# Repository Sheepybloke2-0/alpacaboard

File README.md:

# Alpaca-board
An Open Source keyboard designed for Kailh Low Profile Switches.

This keyboard is meant to be ultra portable, using the [Kailh Low Profile](https://novelkeys.xyz/products/kailh-low-profile-switches)
switches and a minimalist design. That being said, I wanted to add all the keys that I miss when typing on my 40% and 60% boards, such as arrow
keys, Home, End, Delete, Up and Down. I also decided to use USB C as the connector, since I perfer the form factor and flexablility for future
designs. The keyboard will be fully customizable through QMK, the software of which will be coming up soon.

# Goals
 - Be portable yet useful
 - Have RGB underglow, maybe backlighting?
 - Try out different PCB and key layouts for something new and exciting
 - Utilize current Kailh Low Profile switches and keycaps 
 - Add Bluetooth capablilities!

# Software and Tools
Schematic and PCB design was done in [KiCAD](http://kicad-pcb.org/). Because I'm lazy, the routing was done by [Freerouting](https://github.com/freerouting/freerouting).

# References
 - [ATmega32U4 Datasheet](https://cdn.sparkfun.com/datasheets/Dev/Arduino/Boards/ATMega32U4.pdf)
 - [PJRC Wiki](https://www.pjrc.com/)
 - [OLKB Basic Schematics](https://github.com/olkb/olkb_parts/blob/master/planck/schematic.pdf)
    - Used this as a basic reference on how to use the ATmega in the system. Great starting point for figuring out what to Google!
 - [Kailh Low Profile CAD](https://github.com/keyboardio/keyswitch_documentation/blob/master/datasheets/Kailh/PG135001D02.pdf)
    - I believe this is still the design of the current switches. 
 - [QMK's handwiring guide](https://docs.qmk.fm/#/hand_wire)
    - Helps you understand the basics of keyboard design and the key matrix
 - [USB C connector pinouts](https://en.wikipedia.org/wiki/USB-C#Connector_pinouts)
 - [Guide to the key matrix](http://blog.komar.be/how-to-make-a-keyboard-the-matrix/)
    - Great and informative guide to keyboard design
 - [Featherwing ATmega32u4 with BLE](https://www.adafruit.com/product/2829)
 - [MCP23008 I2C GPIO Expander](https://www.adafruit.com/product/593)
 - [Max keyboard key size chart](http://www.maxkeyboard.com/mechanical-keycap-layout-and-size-chart.html)
 - [Bunch of keyboard parts](https://github.com/keebio/Keebio-Parts.pretty)
 - [Featherwing KiCAD Model](https://forum.kicad.info/t/designing-featherwings-in-kicad/6115/2)
    - Use the bottom one
    
# Version 0.2 
After making the schematic and layout for V0.1, I decided to change the components to thru-hole and use a micro-controller for 
easier soldering and assembly. The other reason is because of the Featherwing ATMega32u4 with BLE support. This has a handle
LiPo charging circuit and BLE support for most devices, specifically mobile. For some computers a converter may be needed. 
However, in order to make this work, I had to add a GPIO expander, since most of the pins on the Featherwing are needed for
other functions, such as the Bluetooth and charging. The expander talks via I2C and is addressed at `000`. This expander also
allows for the RGB underglow I wanted to include. Now, it's on to fabrication and software!

# License
I hope that by keeping this project Open Source, other designers can use my work as a base to get up and running quickly. Feel free to use my 
notes and ideas, but please adhere to the [Open Hardware License](https://www.oshwa.org/definition/).

Enjoy!

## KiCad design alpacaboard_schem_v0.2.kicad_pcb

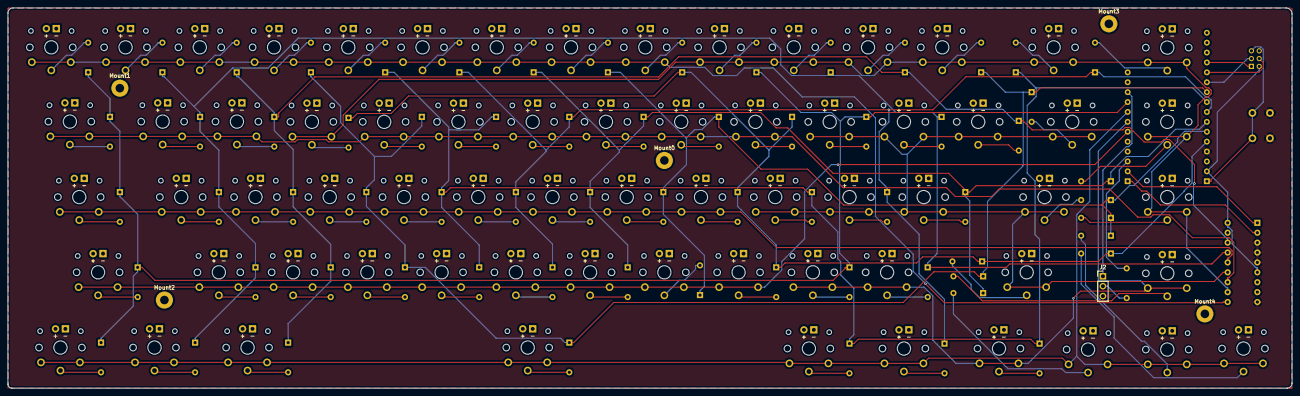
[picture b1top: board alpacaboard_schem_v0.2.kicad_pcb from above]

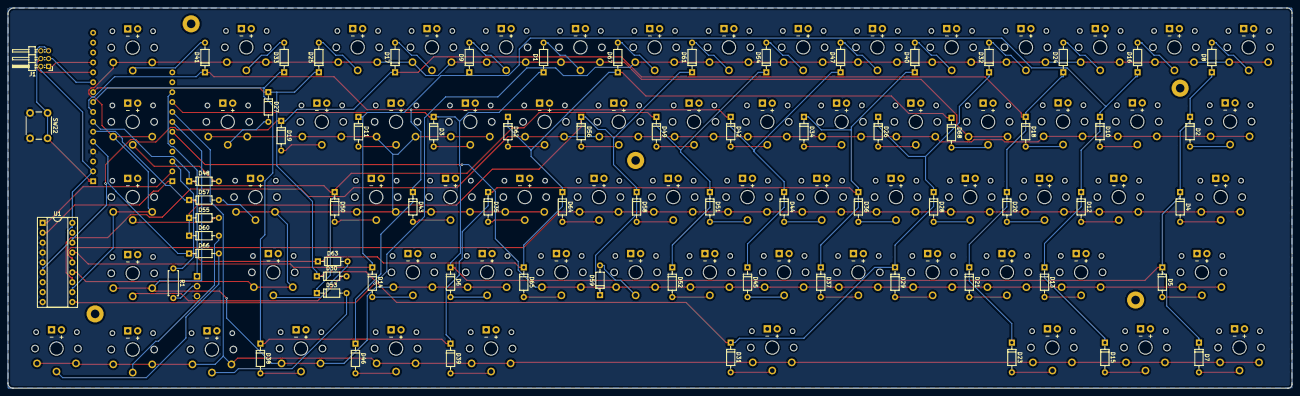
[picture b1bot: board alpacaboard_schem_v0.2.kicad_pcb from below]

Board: 2 copper layers, 329.4 x 97.5 mm, 145 parts (72 on the bottom side), 95 nets.

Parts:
D1, D2, D3, D4, D5, D6, D7, D8, D9, D10, D11, D12, D13, D14, D15, D16, D17, D18, D19, D20, D21, D23, D24, D25, D26, D27, D28, D29, D30, D31, D32, D33, D34, D35, D36, D37, D38, D39, D40, D41, D42, D43, D44, D45, D46, D47, D48, D49, D50, D51, D52, D53, D54, D55, D56, D57, D58, D59, D60, D61, D62, D63, D64, D65, D66, D67, D68: D; D_DO-35_SOD27_P7.62mm_Horizontal
J1: Conn_02x03_Odd_Even; Pin_Header_Angled_2x03_Pitch2.00mm
J2: Conn_01x03_Female; Socket_Strip_Straight_1x03_Pitch2.54mm
MS1: FEATHERWING; PCB_FeatherWing
Mount0, Mount1, Mount2, Mount3, Mount4: MountingHole_2.2mm_M2_Pad
R1: 470; R_Axial_DIN0207_L6.3mm_D2.5mm_P7.62mm_Horizontal
SW1: SW_9; Kailh-PG1350-1u-reversible-flip
SW2: SW_Tab; Kailh-PG1350-1u-reversible-flip
SW3: SW_P; Kailh-PG1350-1u-reversible-flip
SW4: SW_Caps; Kailh-PG1350-1u-reversible-flip
SW5: SW_LShift; Kailh-PG1350-1u-reversible-flip
SW6: SW_Period; Kailh-PG1350-1u-reversible-flip
SW7: SW_LCtl; Kailh-PG1350-1u-reversible-flip
SW8: SW_ESC; Kailh-PG1350-1u-reversible-flip
SW9: SW_0; Kailh-PG1350-1u-reversible-flip
SW10: SW_Q; Kailh-PG1350-1u-reversible-flip
SW11: SW_LBrack; Kailh-PG1350-1u-reversible-flip
SW12: SW_A; Kailh-PG1350-1u-reversible-flip
SW13: SW_Z; Kailh-PG1350-1u-reversible-flip
SW14: SW_FSlash; Kailh-PG1350-1u-reversible-flip
SW15: SW_Meta; Kailh-PG1350-1u-reversible-flip
SW16: SW_1; Kailh-PG1350-1u-reversible-flip
SW17: SW_Minus; Kailh-PG1350-1u-reversible-flip
SW18: SW_W; Kailh-PG1350-1u-reversible-flip
SW19: SW_RBrack; Kailh-PG1350-1u-reversible-flip
SW20: SW_S; Kailh-PG1350-1u-reversible-flip
SW21: SW_X; Kailh-PG1350-1u-reversible-flip
SW22: SW_Push; SW_PUSH_6mm
SW23: SW_LAlt; Kailh-PG1350-1u-reversible-flip
SW24: SW_2; Kailh-PG1350-1u-reversible-flip
SW25: SW_Plus; Kailh-PG1350-1u-reversible-flip
SW26: SW_R; Kailh-PG1350-1u-reversible-flip
SW27: SW_BSlash; Kailh-PG1350-1u-reversible-flip
SW28: SW_D; Kailh-PG1350-1u-reversible-flip
SW29: SW_C; Kailh-PG1350-1u-reversible-flip
SW30: SW_Up; Kailh-PG1350-1u-reversible-flip
SW31: SW_Space; Kailh-PG1350-1u-reversible-flip
SW32: SW_3; Kailh-PG1350-1u-reversible-flip
SW33: SW_Back; Kailh-PG1350-1u-reversible-flip
SW34: SW_T; Kailh-PG1350-1u-reversible-flip
SW35: SW_L; Kailh-PG1350-1u-reversible-flip
SW36: SW_F; Kailh-PG1350-1u-reversible-flip
SW37: SW_V; Kailh-PG1350-1u-reversible-flip
SW38: SW_FN; Kailh-PG1350-1u-reversible-flip
SW39: SW_RAlt; Kailh-PG1350-1u-reversible-flip
SW40: SW_4; Kailh-PG1350-1u-reversible-flip
SW41: SW_Del; Kailh-PG1350-1u-reversible-flip
SW42: SW_Y; Kailh-PG1350-1u-reversible-flip
SW43: SW_SColon; Kailh-PG1350-1u-reversible-flip
SW44: SW_G; Kailh-PG1350-1u-reversible-flip
SW45: SW_B; Kailh-PG1350-1u-reversible-flip
SW46: SW_RCtl; Kailh-PG1350-1u-reversible-flip
SW47: SW_5; Kailh-PG1350-1u-reversible-flip
SW48: SW_Home; Kailh-PG1350-1u-reversible-flip
SW49: SW_U; Kailh-PG1350-1u-reversible-flip
SW50: SW_Quote; Kailh-PG1350-1u-reversible-flip
SW51: SW_H; Kailh-PG1350-1u-reversible-flip
SW52: SW_N; Kailh-PG1350-1u-reversible-flip
SW53: SW_Left; Kailh-PG1350-1u-reversible-flip
SW54: SW_6; Kailh-PG1350-1u-reversible-flip
SW55: SW_End; Kailh-PG1350-1u-reversible-flip
SW56: SW_I; Kailh-PG1350-1u-reversible-flip
SW57: SW_Enter; Kailh-PG1350-1u-reversible-flip
SW58: SW_J; Kailh-PG1350-1u-reversible-flip
SW59: SW_M; Kailh-PG1350-1u-reversible-flip
SW60: SW_Down; Kailh-PG1350-1u-reversible-flip
SW61: SW_7; Kailh-PG1350-1u-reversible-flip
SW62: SW_O; Kailh-PG1350-1u-reversible-flip
SW63: SW_RShift; Kailh-PG1350-1u-reversible-flip
SW64: SW_K; Kailh-PG1350-1u-reversible-flip
SW65: SW_Comma; Kailh-PG1350-1u-reversible-flip
SW66: SW_Right; Kailh-PG1350-1u-reversible-flip
SW67: SW_8; Kailh-PG1350-1u-reversible-flip
SW69: SW_E; Kailh-PG1350-1u-reversible-flip
U1: MCP23008; DIP-18_W7.62mm_Socket

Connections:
+5Vcc: J2.1, MS1.26
C0: D1.1, D2.1, D3.1, D4.1, D5.1, D6.1, D7.1, D8.1, MS1.25
C1: D9.1, D10.1, D11.1, D12.1, D13.1, D14.1, D15.1, D16.1, U1.15
C2: D17.1, D18.1, D19.1, D20.1, D21.1, D23.1, D24.1, U1.16
C3: D25.1, D26.1, D27.1, D28.1, D29.1, D30.1, D31.1, D32.1, MS1.10
C4: D33.1, D34.1, D35.1, D36.1, D37.1, D38.1, D39.1, D40.1, MS1.9
C5: D41.1, D42.1, D43.1, D44.1, D45.1, D46.1, D47.1, MS1.8
C6: D48.1, D49.1, D50.1, D51.1, D52.1, D53.1, D54.1, MS1.7
C7: D55.1, D56.1, D57.1, D58.1, D59.1, D60.1, D61.1, MS1.6
C8: D62.1, D63.1, D64.1, D65.1, D66.1, D67.1, D68.1, MS1.5
GNDREF: J1.6, J2.3, MS1.4, SW22.2, U1.3, U1.4, U1.5, U1.9
LED_DATA: J2.2, R1.2
MISO: J1.1, MS1.13
MOSI: J1.4, MS1.12
unnamed: D1.2, SW1.1
unnamed: D2.2, SW2.1
unnamed: D3.2, SW3.1
unnamed: D4.2, SW4.1
unnamed: D5.2, SW5.1
unnamed: D6.2, SW6.1
unnamed: D7.2, SW7.1
unnamed: D8.2, SW8.1
unnamed: D9.2, SW9.1
unnamed: D10.2, SW10.1
unnamed: D11.2, SW11.1
unnamed: D12.2, SW12.1
unnamed: D13.2, SW13.1
unnamed: D14.2, SW14.1
unnamed: D15.2, SW15.1
unnamed: D16.2, SW16.1
unnamed: D17.2, SW17.1
unnamed: D18.2, SW18.1
unnamed: D19.2, SW19.1
unnamed: D20.2, SW20.1
unnamed: D21.2, SW21.1
unnamed: D23.2, SW23.1
unnamed: D24.2, SW24.1
unnamed: D25.2, SW25.1
unnamed: D26.2, SW26.1
unnamed: D27.2, SW27.1
unnamed: D28.2, SW28.1
unnamed: D29.2, SW29.1
unnamed: D30.2, SW30.1
unnamed: D31.2, SW31.1
unnamed: D32.2, SW32.1
unnamed: D33.2, SW33.1
unnamed: D34.2, SW34.1
unnamed: D35.2, SW35.1
unnamed: D36.2, SW36.1
unnamed: D37.2, SW37.1
unnamed: D38.2, SW38.1
unnamed: D39.2, SW39.1
unnamed: D40.2, SW40.1
unnamed: D41.2, SW41.1
unnamed: D42.2, SW42.1
unnamed: D43.2, SW43.1
unnamed: D44.2, SW44.1
unnamed: D45.2, SW45.1
unnamed: D46.2, SW46.1
unnamed: D47.2, SW47.1
unnamed: D48.2, SW48.1
unnamed: D49.2, SW49.1
unnamed: D50.2, SW50.1
unnamed: D51.2, SW51.1
unnamed: D52.2, SW52.1
unnamed: D53.2, SW53.1
unnamed: D54.2, SW54.1
unnamed: D55.2, SW55.1
unnamed: D56.2, SW56.1
unnamed: D57.2, SW57.1
unnamed: D58.2, SW58.1
unnamed: D59.2, SW59.1
unnamed: D60.2, SW60.1
unnamed: D61.2, SW61.1
unnamed: D62.2, SW62.1
unnamed: D63.2, SW63.1
unnamed: D64.2, SW64.1
unnamed: D65.2, SW65.1
unnamed: D66.2, SW66.1
unnamed: D67.2, SW67.1
unnamed: D68.2, SW69.1
unnamed: MS1.19, R1.1
R0: SW8.2, SW16.2, SW24.2, SW32.2, SW40.2, SW47.2, SW54.2, SW61.2, SW67.2, U1.10
R1: SW1.2, SW9.2, SW17.2, SW25.2, SW33.2, SW41.2, SW48.2, SW55.2, SW69.2, U1.11
R2: SW2.2, SW10.2, SW18.2, SW26.2, SW34.2, SW42.2, SW49.2, SW56.2, SW62.2, U1.12
R3: SW3.2, SW11.2, SW19.2, SW27.2, SW35.2, SW43.2, SW50.2, SW57.2, SW63.2, U1.13
R4: SW4.2, SW12.2, SW20.2, SW28.2, SW36.2, SW44.2, SW51.2, SW58.2, SW64.2, U1.14
R5: MS1.22, SW5.2, SW13.2, SW21.2, SW29.2, SW37.2, SW45.2, SW52.2, SW59.2, SW65.2
R6: MS1.23, SW6.2, SW14.2, SW30.2, SW38.2
R7: MS1.24, SW7.2, SW15.2, SW23.2, SW31.2, SW39.2, SW46.2, SW53.2, SW60.2, SW66.2
RESET_N: J1.5, MS1.1, SW22.1
SCK: J1.3, MS1.11
SCL: MS1.18, U1.1
SDA: MS1.17, U1.2
Vcc: J1.2, MS1.2, U1.6, U1.18

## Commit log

2018-06-07 Created an initial README
2018-06-07 Added Rev 0.1
2018-06-07 Updated with more sections
2018-06-11 Added Version 0.2
